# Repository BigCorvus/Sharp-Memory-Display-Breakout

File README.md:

# Sharp-Memory-Display-Breakout
Breakout for the AYF531035A 10pin 0.5mm pitch connector which mates with the Shar Memory Displays and also the good old  LPM013M126A

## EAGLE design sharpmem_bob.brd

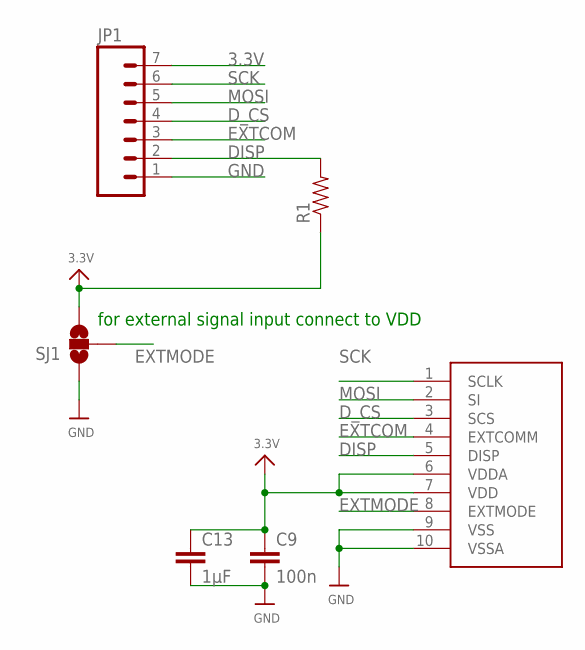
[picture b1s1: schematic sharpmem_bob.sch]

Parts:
C9: 100n; C0402
C13: 1µF; C0402
JP1: M07; 1X07
R1: RESISTOR0402-RES; 0402-RES
SJ1: SOLDERJUMPER_2WAYS; SJ_3
U$2: SHARP_MEM_DISP; Y5BW

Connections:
3.3V: C9.1, C13.1, JP1.7, R1.1, SJ1.3, U$2.6 (VDDA), U$2.7 (VDD)
DISP: JP1.2, R1.2, U$2.5 (DISP)
D_CS: JP1.4, U$2.3 (SCS)
EXTCOM: JP1.3, U$2.4 (EXTCOMM)
EXTMODE: SJ1.2, U$2.8 (EXTMODE)
GND: C9.2, C13.2, JP1.1, SJ1.1, U$2.9 (VSS), U$2.10 (VSSA)
MOSI: JP1.5, U$2.2 (SI)
SCK: JP1.6, U$2.1 (SCLK)

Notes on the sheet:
for external signal input connect to VDD

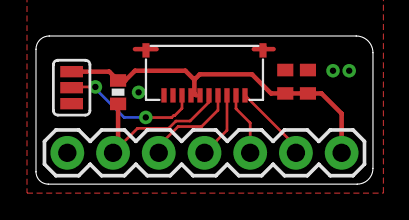
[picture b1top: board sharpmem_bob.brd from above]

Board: 2 copper layers, 18.7 x 8.2 mm, 6 parts (0 on the bottom side), 8 nets.

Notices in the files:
parts and their libraries:
SparkFun-Connectors: Licensing: Creative Commons ShareAlike 4.0 International - https://creativecommons.org/licenses/by-sa/4.0
microbuilder: This work is placed in the public domain, and may be freely used for commercial and non-commercial work with the following conditions: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
